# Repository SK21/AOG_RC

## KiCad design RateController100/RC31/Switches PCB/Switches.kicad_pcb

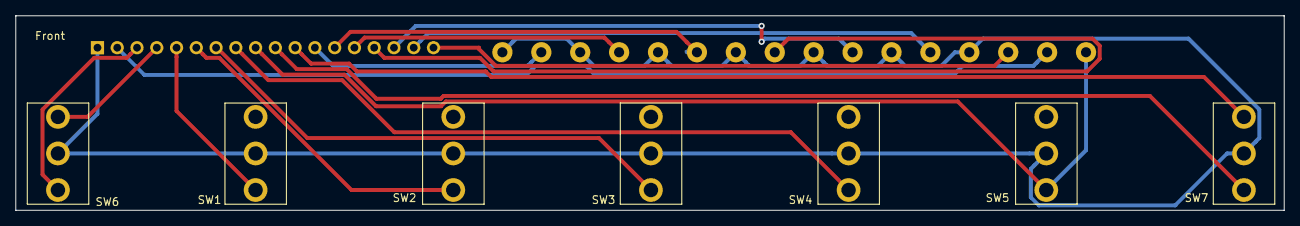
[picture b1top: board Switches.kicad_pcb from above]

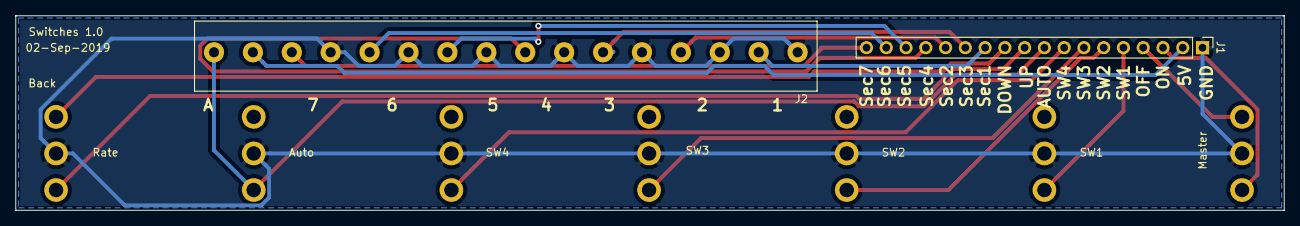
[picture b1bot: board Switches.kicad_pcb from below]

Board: 2 copper layers, 163.0 x 25.0 mm, 9 parts (2 on the bottom side), 18 nets.

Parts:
J1: Conn_01x18_Female; PinHeader_1x18_P2.54mm_Vertical
J2: LED terminals; Phoenix_16_pin_5mm_terminal_block
SW1: SW1; Mini_Toggle_3pin
SW2: SW2; Mini_Toggle_3pin
SW3: SW3; Mini_Toggle_3pin
SW4: SW4; Mini_Toggle_3pin
SW5: Auto; Mini_Toggle_3pin
SW6: Master; Mini_Toggle_3pin
SW7: Rate; Mini_Toggle_3pin

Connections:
unnamed: J1.1, J2.1, J2.3, J2.5, J2.7, J2.9, J2.11, J2.13, SW1.2, SW2.2, SW3.2, SW4.2, SW5.2, SW6.2, SW7.2
unnamed: J1.2, J2.15
unnamed: J1.3, SW6.3
unnamed: J1.4, SW6.1
unnamed: J1.5, SW1.3
unnamed: J1.6, SW2.3
unnamed: J1.7, SW3.3
unnamed: J1.8, SW4.3
unnamed: J1.9, J2.16, SW5.3
unnamed: J1.10, SW7.3
unnamed: J1.11, SW7.1
unnamed: J1.12, J2.2
unnamed: J1.13, J2.6
unnamed: J1.14, J2.4
unnamed: J1.15, J2.8
unnamed: J1.16, J2.10
unnamed: J1.17, J2.12
unnamed: J1.18, J2.14
